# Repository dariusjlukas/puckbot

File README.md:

# puckbot
Puck-shaped robot design files and source code

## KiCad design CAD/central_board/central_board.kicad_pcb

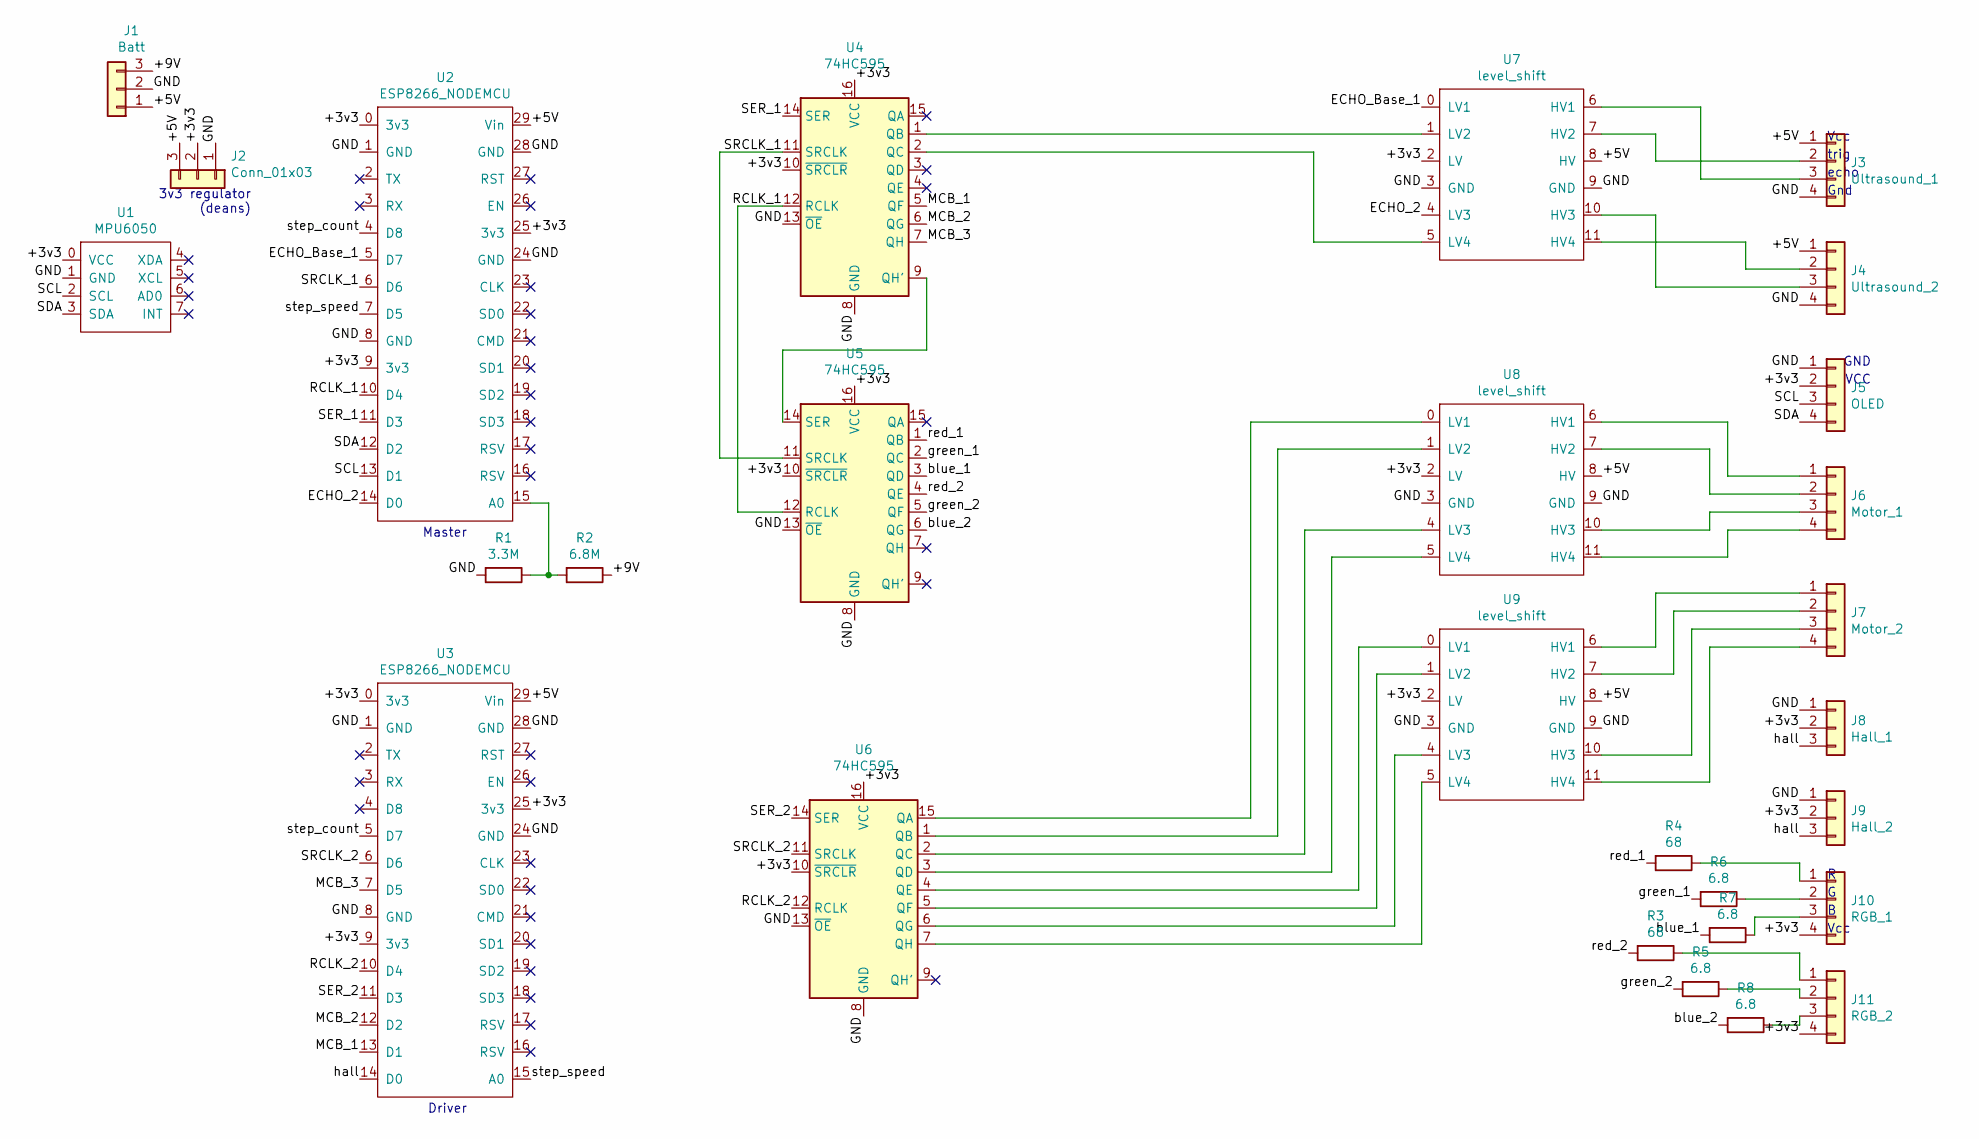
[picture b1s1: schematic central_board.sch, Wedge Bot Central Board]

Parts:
J1: Batt; JST_XHP_3
J2: Conn_01x03; JST_XHP_3
J3: Ultrasound_1; JST_XHP_4
J4: Ultrasound_2; JST_XHP_4
J5: OLED; JST_XHP_4
J6: Motor_1; JST_XHP_4
J7: Motor_2; JST_XHP_4
J8: Hall_1; JST_XHP_3
J9: Hall_2; JST_XHP_3
J10: RGB_1; JST_XHP_4
J11: RGB_2; JST_XHP_4
R1: 3.3M; R_Axial_DIN0207_L6.3mm_D2.5mm_P7.62mm_Horizontal
R2: 6.8M; R_Axial_DIN0207_L6.3mm_D2.5mm_P7.62mm_Horizontal
R3, R4: 68; R_Axial_DIN0207_L6.3mm_D2.5mm_P7.62mm_Horizontal
R5, R6, R7, R8: 6.8; R_Axial_DIN0207_L6.3mm_D2.5mm_P7.62mm_Horizontal
U1: MPU6050
U2, U3: ESP8266_NODEMCU
U4, U5, U6: 74HC595; 74HC595N
U7, U8, U9: level_shift; Level_shift

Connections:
/+3v3: J2.2, J5.2, J8.2, J9.2, J10.4, J11.4, U1.0 (VCC), U2.0 (3v3), U2.9 (3v3), U2.25 (3v3), U3.0 (3v3), U3.9 (3v3), U3.25 (3v3), U4.10 (~SRCLR), U4.16 (VCC), U5.10 (~SRCLR), U5.16 (VCC), U6.10 (~SRCLR), U6.16 (VCC), U7.2 (LV), U8.2 (LV), U9.2 (LV)
/+5V: J1.1, J2.3, J3.1, J4.1, U2.29 (Vin), U3.29 (Vin), U7.8 (HV), U8.8 (HV), U9.8 (HV)
/+9V: J1.3, R2.1
/ECHO_2: U2.14 (D0), U7.4 (LV3)
/ECHO_Base_1: U2.5 (D7), U7.0 (LV1)
/GND: J1.2, J2.1, J3.4, J4.4, J5.1, J8.1, J9.1, R1.2, U1.1 (GND), U2.1 (GND), U2.8 (GND), U2.24 (GND), U2.28 (GND), U3.1 (GND), U3.8 (GND), U3.24 (GND), U3.28 (GND), U4.8 (GND), U4.13 (~OE), U5.8 (GND), U5.13 (~OE), U6.8 (GND), U6.13 (~OE), U7.3 (GND), U7.9 (GND), U8.3 (GND), U8.9 (GND), U9.3 (GND), U9.9 (GND)
/MCB_1: U3.13 (D1), U4.5 (QF)
/MCB_2: U3.12 (D2), U4.6 (QG)
/MCB_3: U3.7 (D5), U4.7 (QH)
/RCLK_1: U2.10 (D4), U4.12 (RCLK), U5.12 (RCLK)
/RCLK_2: U3.10 (D4), U6.12 (RCLK)
/SCL: J5.3, U1.2 (SCL), U2.13 (D1)
/SDA: J5.4, U1.3 (SDA), U2.12 (D2)
/SER_1: U2.11 (D3), U4.14 (SER)
/SER_2: U3.11 (D3), U6.14 (SER)
/SRCLK_1: U2.6 (D6), U4.11 (SRCLK), U5.11 (SRCLK)
/SRCLK_2: U3.6 (D6), U6.11 (SRCLK)
/blue_1: R7.2, U5.3 (QD)
/blue_2: R8.2, U5.6 (QG)
/green_1: R6.2, U5.2 (QC)
/green_2: R5.2, U5.5 (QF)
/hall: J8.3, J9.3, U3.14 (D0)
/red_1: R4.2, U5.1 (QB)
/red_2: R3.2, U5.4 (QE)
/step_count: U2.4 (D8), U3.5 (D7)
/step_speed: U2.7 (D5), U3.15 (A0)
unnamed: J3.2, U7.7 (HV2)
unnamed: J3.3, U7.6 (HV1)
unnamed: J4.2, U7.11 (HV4)
unnamed: J4.3, U7.10 (HV3)
unnamed: J6.1, U8.6 (HV1)
unnamed: J6.2, U8.7 (HV2)
unnamed: J6.3, U8.10 (HV3)
unnamed: J6.4, U8.11 (HV4)
unnamed: J7.1, U9.6 (HV1)
unnamed: J7.2, U9.7 (HV2)
unnamed: J7.3, U9.10 (HV3)
unnamed: J7.4, U9.11 (HV4)
unnamed: J10.1, R4.1
unnamed: J10.2, R6.1
unnamed: J10.3, R7.1
unnamed: J11.1, R3.1
unnamed: J11.2, R5.1
unnamed: J11.3, R8.1
unnamed: R1.1, R2.2, U2.15 (A0)
unnamed: U4.1 (QB), U7.1 (LV2)
unnamed: U4.2 (QC), U7.5 (LV4)
unnamed: U4.9 (QH'), U5.14 (SER)
unnamed: U6.1 (QB), U8.1 (LV2)
unnamed: U6.2 (QC), U8.4 (LV3)
unnamed: U6.3 (QD), U8.5 (LV4)
unnamed: U6.4 (QE), U9.0 (LV1)
unnamed: U6.5 (QF), U9.1 (LV2)
unnamed: U6.6 (QG), U9.4 (LV3)
unnamed: U6.7 (QH), U9.5 (LV4)
unnamed: U6.15 (QA), U8.0 (LV1)

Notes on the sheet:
Master
Driver
Vcc
trig
echo
Gnd
3v3 regulator (deans)
GND
VCC

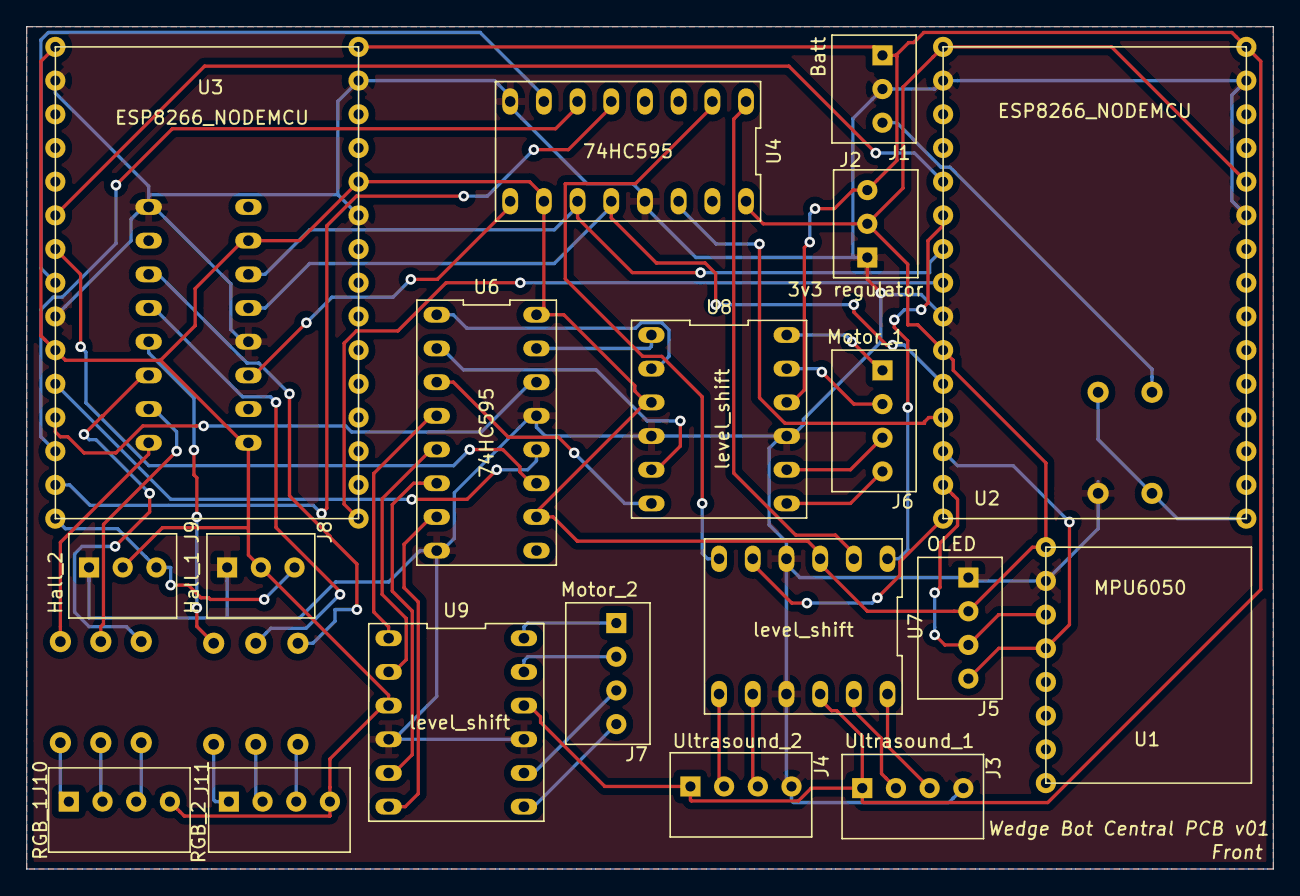
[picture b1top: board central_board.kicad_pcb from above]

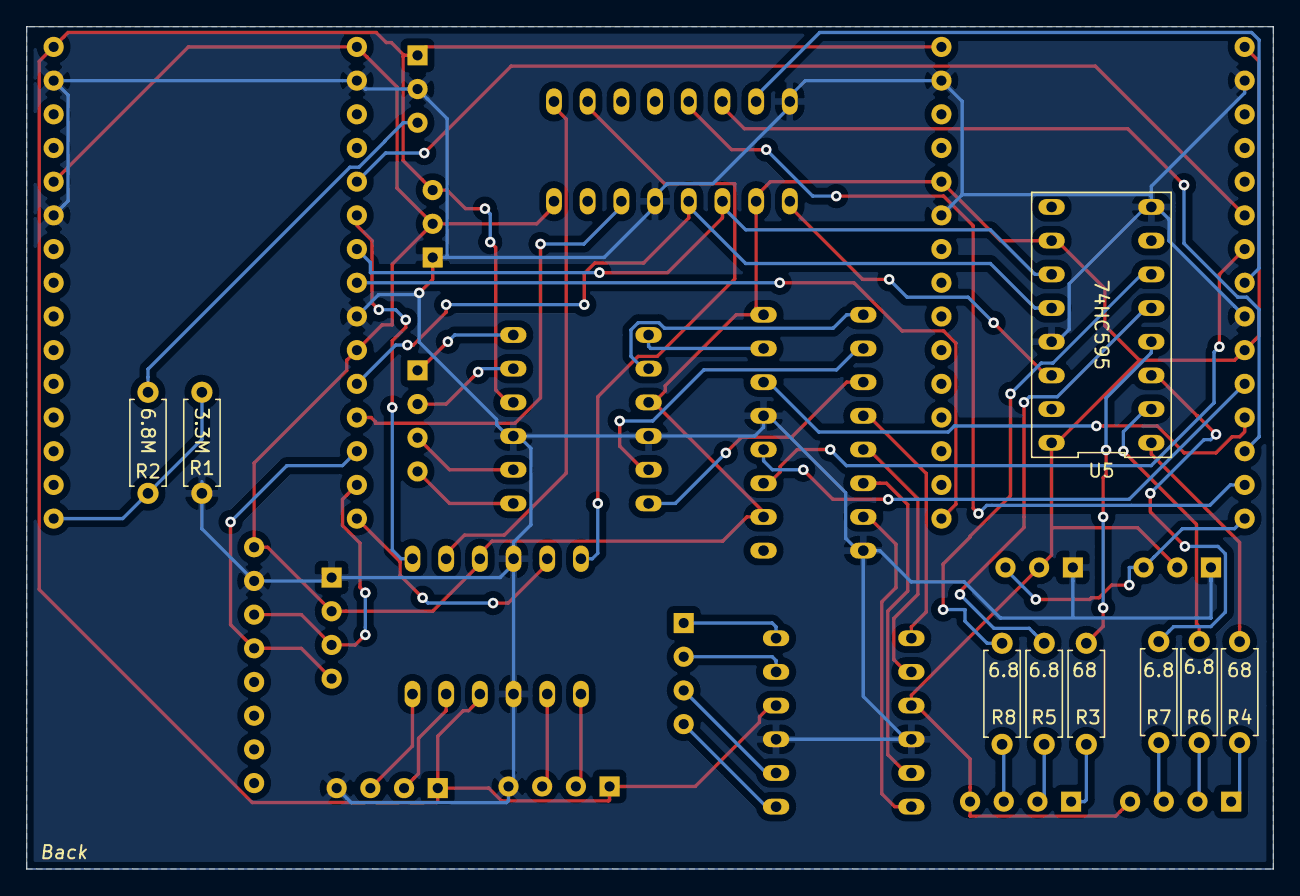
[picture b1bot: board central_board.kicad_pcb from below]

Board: 2 copper layers, 94.0 x 63.5 mm, 28 parts (9 on the bottom side), 56 nets.

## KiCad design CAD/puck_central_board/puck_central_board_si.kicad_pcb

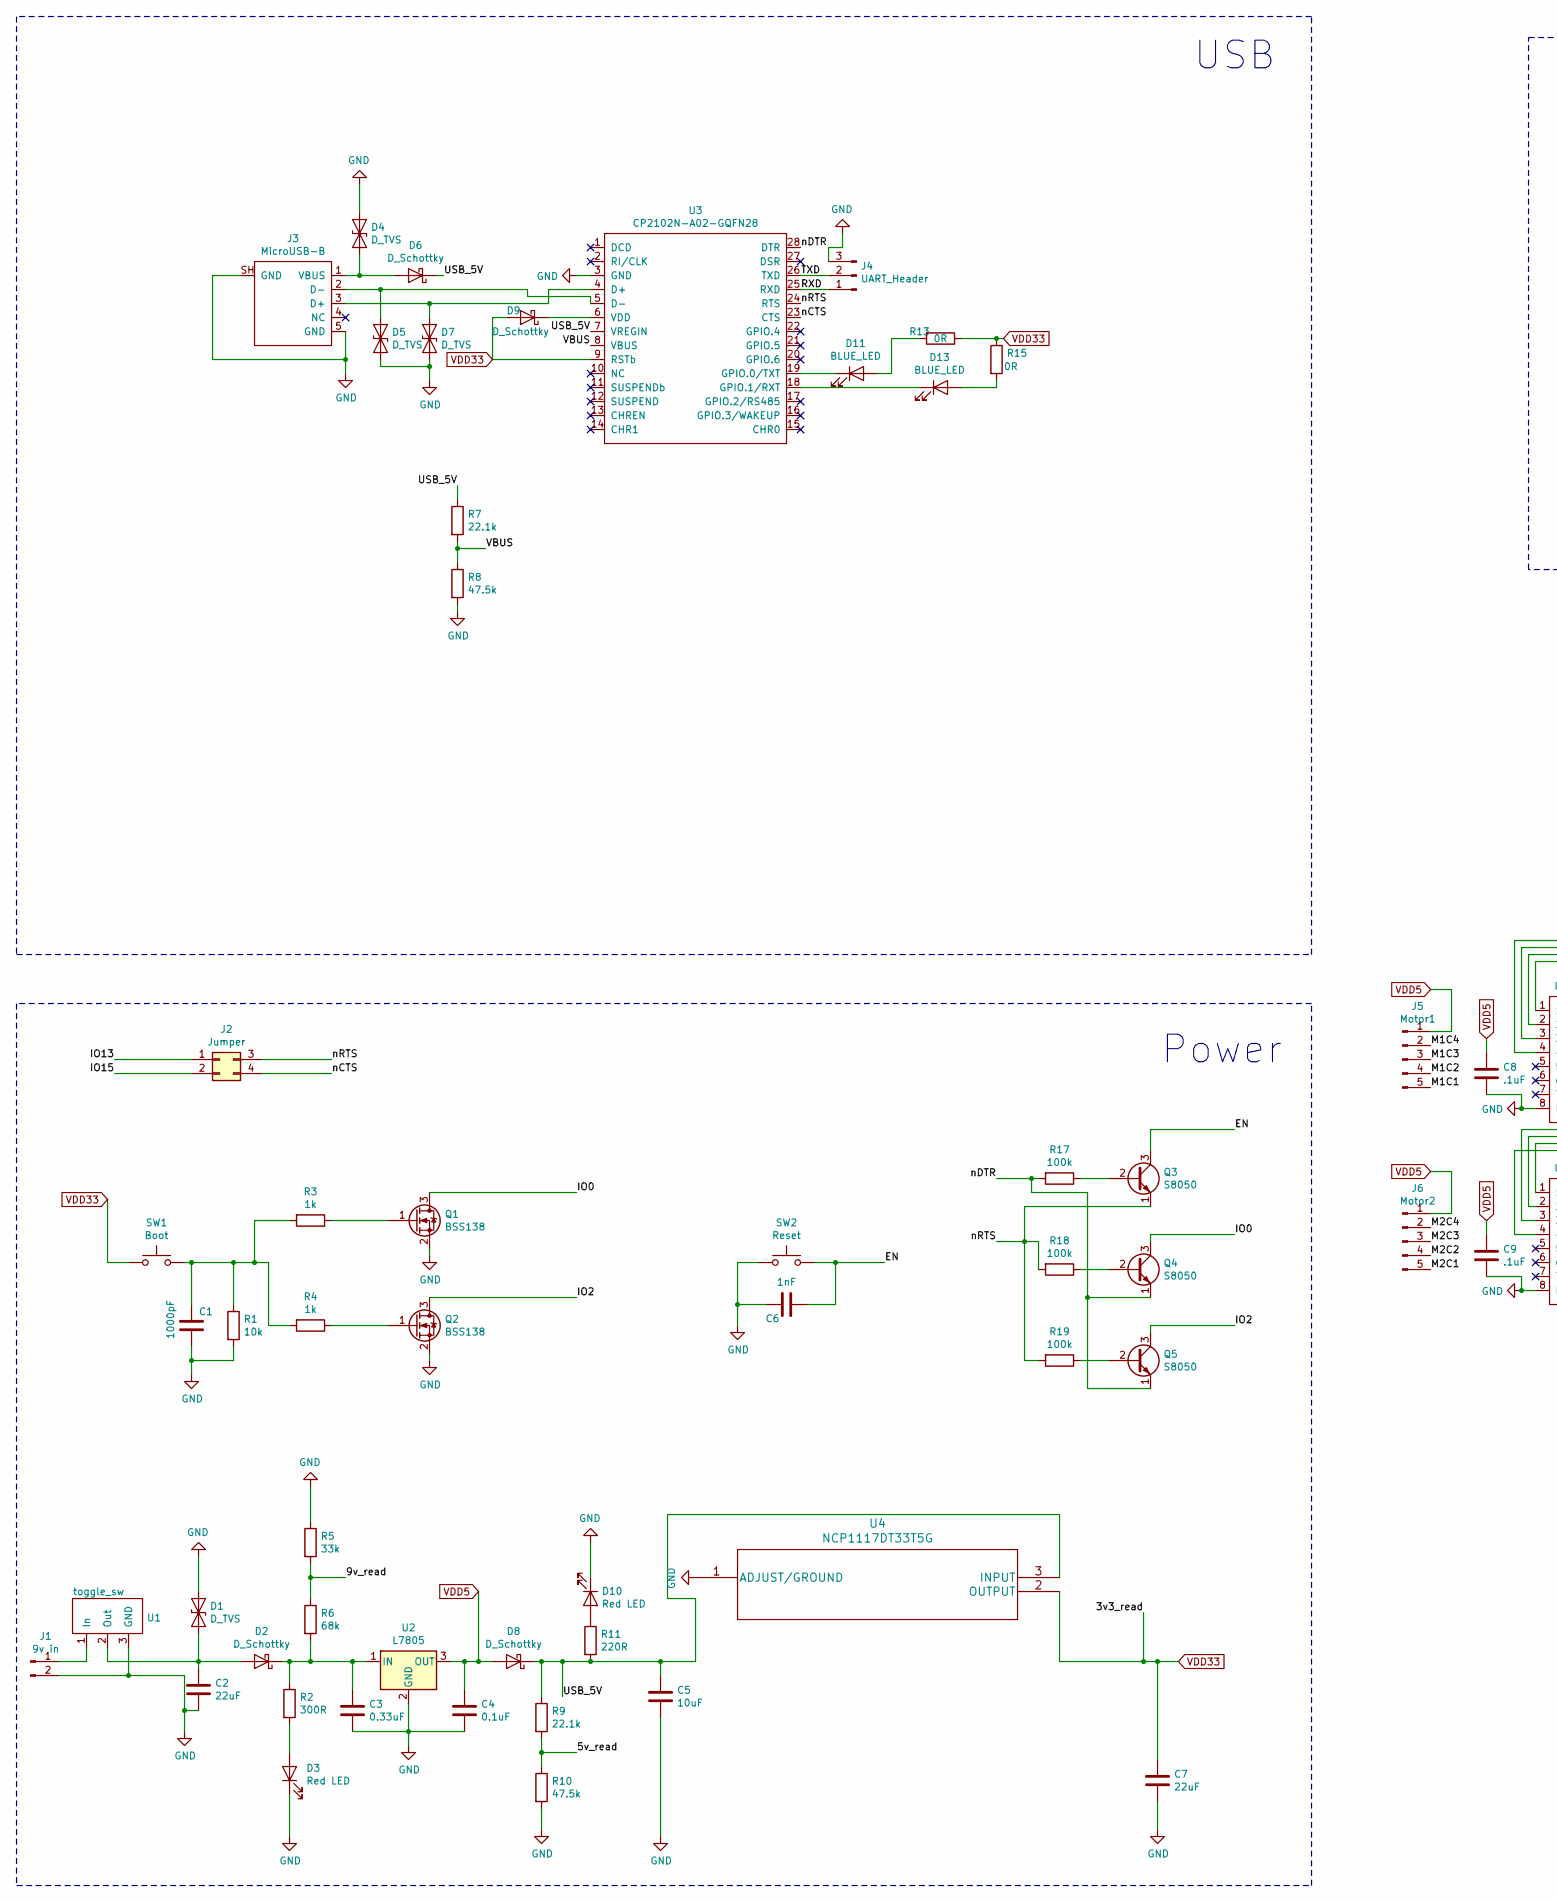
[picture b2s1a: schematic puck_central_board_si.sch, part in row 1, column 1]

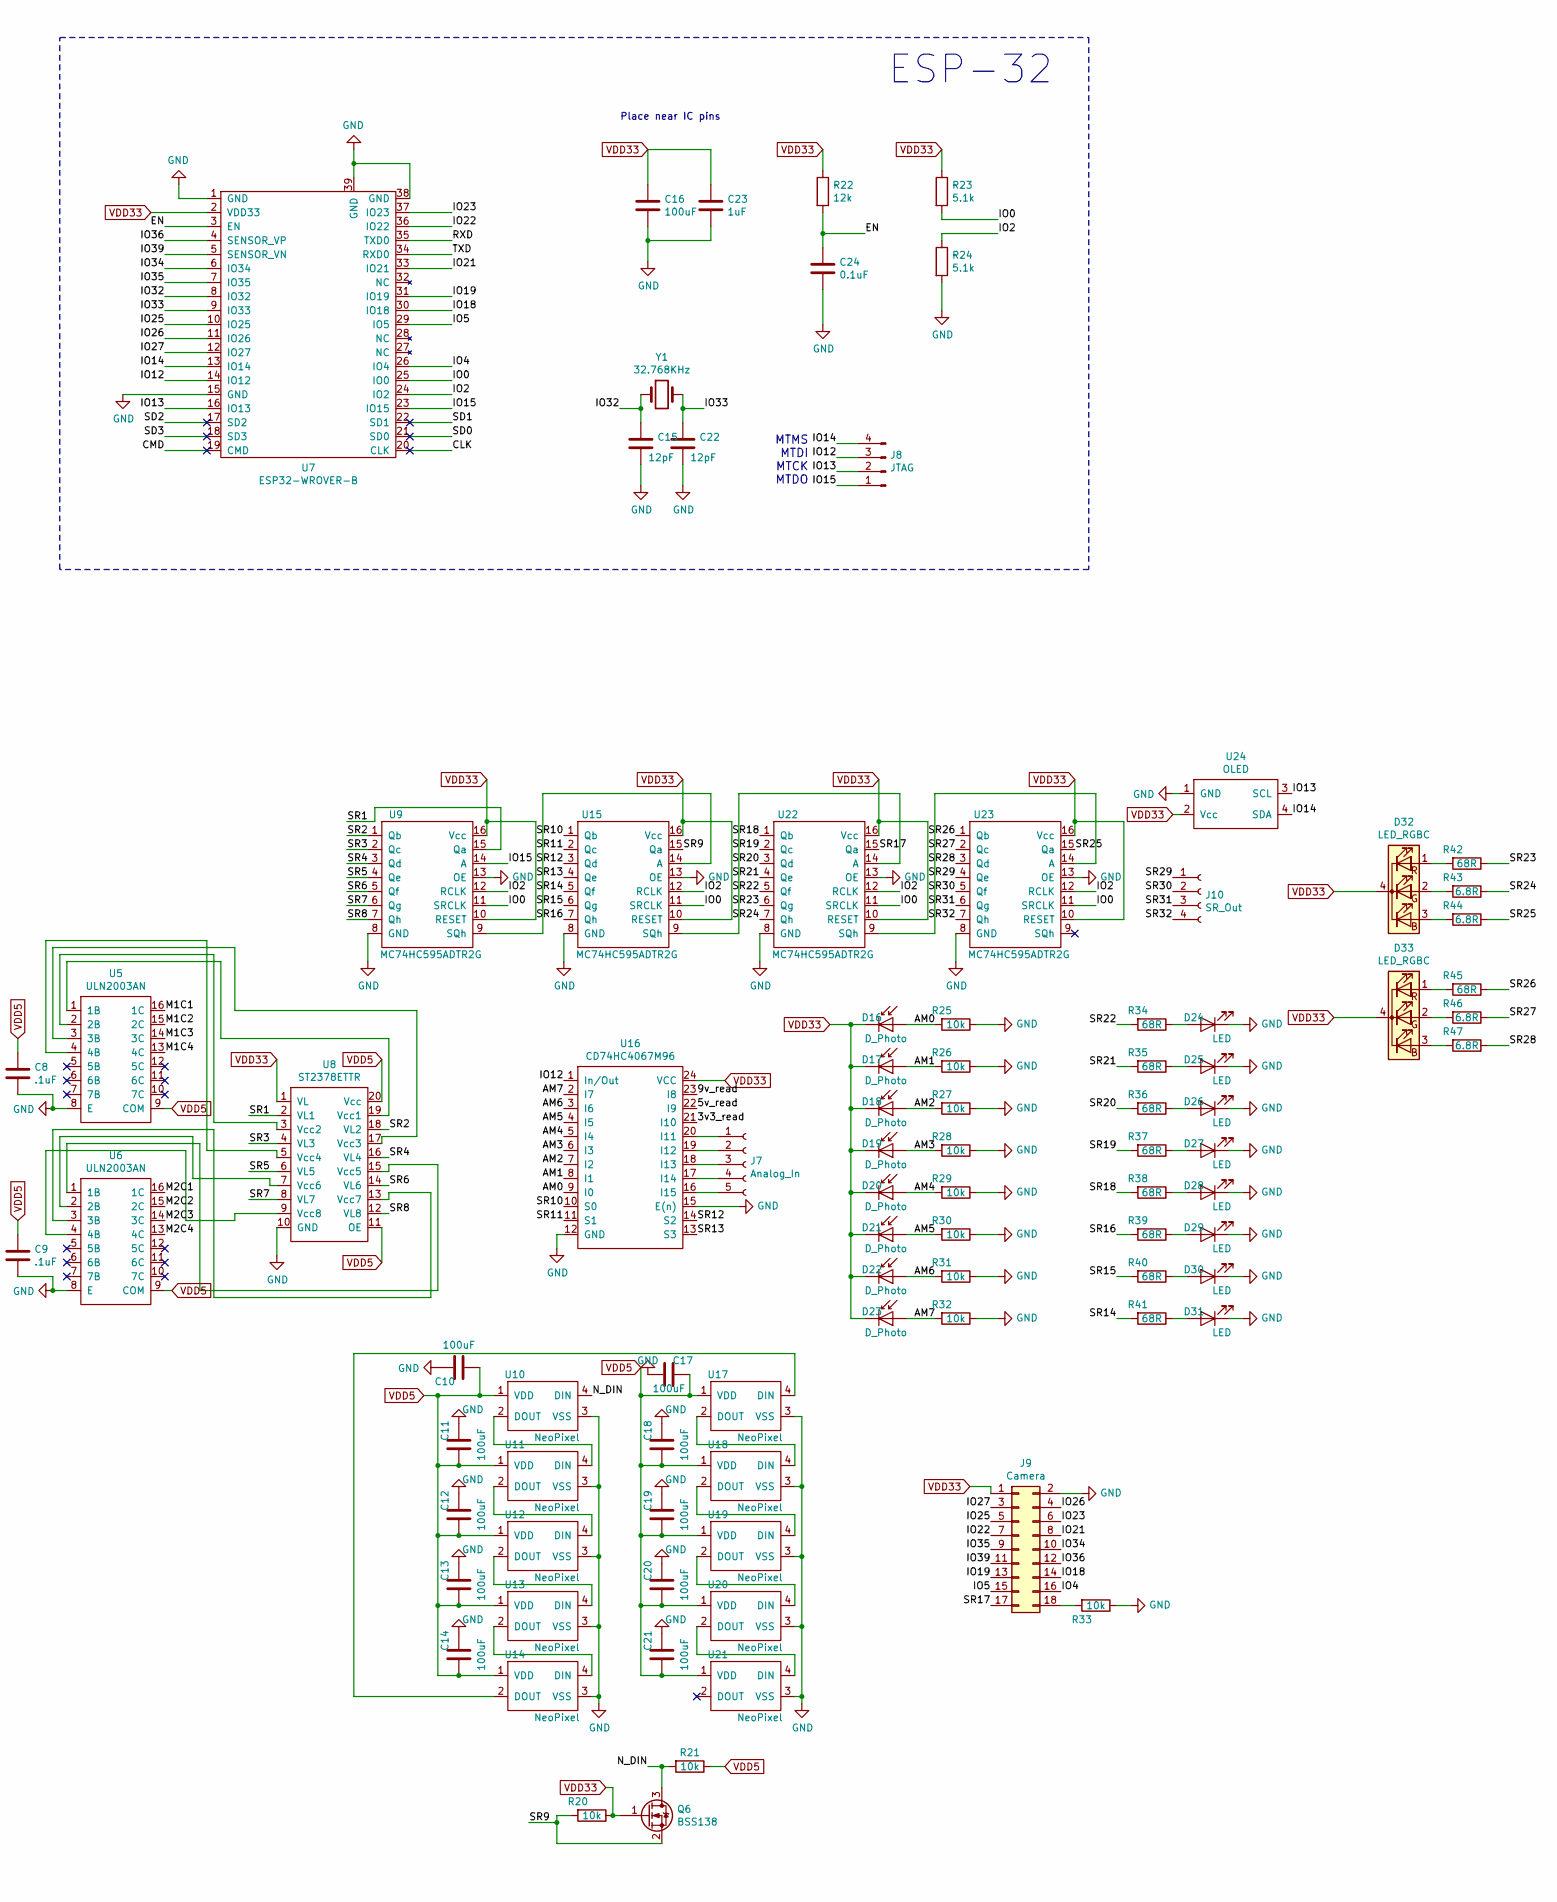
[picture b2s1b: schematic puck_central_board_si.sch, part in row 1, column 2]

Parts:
C1: 1000pF; C_0402_1005Metric
C2, C7: 22uF; C_0805_2012Metric
C3: 0.33uF; C_0201_0603Metric
C4, C24: 0.1uF; C_0402_1005Metric
C5: 10uF; C_1206_3216Metric
C6: 1nF; C_0402_1005Metric
C8, C9: .1uF; C_0402_1005Metric
C10, C11, C12, C13, C14, C16, C17, C18, C19, C20, C21: 100uF; C_1206_3216Metric
C15, C22: 12pF; C_0402_1005Metric
C23: 1uF; C_0603_1608Metric
D1, D4, D5, D7: D_TVS; D_SMA
D2, D6, D8, D9: D_Schottky; D_SMA
D3, D10: Red LED; LED_0603
D11, D13: BLUE_LED; LED_0603
D16, D17, D18, D19, D20, D21, D22, D23: D_Photo; LED_5mm_Radial
D24, D25, D26, D27, D28, D29, D30, D31: LED; LED_5mm_Radial
D32, D33: LED_RGBC; RGB_LED
J1: 9v in; JST_XHP_2
J2: Jumper; Jumper_Header
J3: MicroUSB-B; USB_Micro_B_Female_10118193-0001LF
J4: UART_Header; Deans_2.54_3
J5: Motor1; JST_XHP_5
J6: Motor2; JST_XHP_5
J7: Analog_In; Deans_2.54_5
J8: JTAG; Deans_2.54_4
J9: Camera; camera_connector
J10: SR_Out; Deans_2.54_4
Q1, Q2, Q6: BSS138; SOT-23
Q3, Q4, Q5: S8050; SOT-23
R1, R20, R21, R25, R26, R27, R28, R29, R30, R31, R32, R33: 10k; R_0402_1005Metric
R2: 300R; R_0402_1005Metric
R3, R4: 1k; R_0402_1005Metric
R5: 33k; R_0402_1005Metric
R6: 68k; R_0603_1608Metric_Pad1.05x0.95mm_HandSolder
R7, R9: 22.1k; R_0402_1005Metric
R8, R10: 47.5k; R_0402_1005Metric
R11: 220R; R_0402_1005Metric
R13, R15: 0R; R_0402_1005Metric
R17, R18, R19: 100k; R_0402_1005Metric
R22: 12k; R_0402_1005Metric
R23, R24: 5.1k; R_0402_1005Metric
R34, R35, R36, R37, R38, R39, R40, R41, R42, R45: 68R; R_0603_1608Metric_Pad1.05x0.95mm_HandSolder
R43, R44, R46, R47: 6.8R; R_0603_1608Metric
SW1: Boot; SW_Push_1P1T_NO_6x6mm_H9.5mm
SW2: Reset; SW_Push_1P1T_NO_6x6mm_H9.5mm
U1: toggle_sw; Deans_2.54_3
U2: L7805; TO-218-3_Horizontal_TabDown
U3: CP2102N-A02-GQFN28; CP2102_QFN28
U4: NCP1117DT33T5G
U5, U6: ULN2003AN; Socket_DIP-16_7.62mm_Conn
U7: ESP32-WROVER-B
U8: ST2378ETTR; ST2378
U9, U15, U22, U23: MC74HC595ADTR2G
U10, U11, U12, U13, U14, U17, U18, U19, U20, U21: NeoPixel
U16: CD74HC4067M96
U24: OLED; Deans_2.54_4
Y1: 32.768KHz; FC-135R

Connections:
/5v_read: R9.2, R10.1, U16.22 (I9)
/9v_read: R5.2, R6.1, U16.23 (I8)
/AM0: D16.2 (A), R25.2, U16.9 (I0)
/AM1: D17.2 (A), R26.2, U16.8 (I1)
/AM2: D18.2 (A), R27.2, U16.7 (I2)
/AM3: D19.2 (A), R28.2, U16.6 (I3)
/AM4: D20.2 (A), R29.2, U16.5 (I4)
/AM5: D21.2 (A), R30.2, U16.4 (I5)
/AM6: D22.2 (A), R31.2, U16.3 (I6)
/AM7: D23.2 (A), R32.2, U16.2 (I7)
/CLK: U7.20 (CLK)
/CMD: U7.19 (CMD)
/EN: C6.1, C24.1, Q3.3 (C), R22.2, SW2.2, U7.3 (EN)
/IO0: Q1.3 (D), Q4.3 (C), R23.2, U7.25 (IO0), U9.11 (SRCLK), U15.11 (SRCLK), U22.11 (SRCLK), U23.11 (SRCLK)
/IO2: Q2.3 (D), Q5.3 (C), R24.1, U7.24 (IO2), U9.12 (RCLK), U15.12 (RCLK), U22.12 (RCLK), U23.12 (RCLK)
/IO4: J9.16, U7.26 (IO4)
/IO5: J9.15, U7.29 (IO5)
/IO12: J8.3, U7.14 (IO12), U16.1 (In/Out)
/IO13: J2.1, J8.2, U7.16 (IO13), U24.3 (SCL)
/IO14: J8.4, U7.13 (IO14), U24.4 (SDA)
/IO15: J2.2, J8.1, U7.23 (IO15), U9.14 (A)
/IO18: J9.14, U7.30 (IO18)
/IO19: J9.13, U7.31 (IO19)
/IO21: J9.8, U7.33 (IO21)
/IO22: J9.7, U7.36 (IO22)
/IO23: J9.6, U7.37 (IO23)
/IO25: J9.5, U7.10 (IO25)
/IO26: J9.4, U7.11 (IO26)
/IO27: J9.3, U7.12 (IO27)
/IO32: C15.1, U7.8 (IO32), Y1.1
/IO33: C22.1, U7.9 (IO33), Y1.2
/IO34: J9.10, U7.6 (IO34)
/IO35: J9.9, U7.7 (IO35)
/IO36: J9.12, U7.4 (SENSOR_VP)
/IO39: J9.11, U7.5 (SENSOR_VN)
/M1C1: J5.5, U5.16 (1C)
/M1C2: J5.4, U5.15 (2C)
/M1C3: J5.3, U5.14 (3C)
/M1C4: J5.2, U5.13 (4C)
/M2C1: J6.5, U6.16 (1C)
/M2C2: J6.4, U6.15 (2C)
/M2C3: J6.3, U6.14 (3C)
/M2C4: J6.2, U6.13 (4C)
/N_DIN: Q6.3 (D), R21.2, U10.4 (DIN)
/RXD: J4.1, U3.25 (RXD), U7.35 (TXD0)
/SD0: U7.21 (SD0)
/SD1: U7.22 (SD1)
/SD2: U7.17 (SD2)
/SD3: U7.18 (SD3)
/SR1: U8.2 (VL1), U9.15 (Qa)
/SR2: U8.18 (VL2), U9.1 (Qb)
/SR3: U8.4 (VL3), U9.2 (Qc)
/SR4: U8.16 (VL4), U9.3 (Qd)
/SR5: U8.6 (VL5), U9.4 (Qe)
/SR6: U8.14 (VL6), U9.5 (Qf)
/SR7: U8.8 (VL7), U9.6 (Qg)
/SR8: U8.12 (VL8), U9.7 (Qh)
/SR9: Q6.2 (S), R20.2, U15.15 (Qa)
/SR10: U15.1 (Qb), U16.10 (S0)
/SR11: U15.2 (Qc), U16.11 (S1)
/SR12: U15.3 (Qd), U16.14 (S2)
/SR13: U15.4 (Qe), U16.13 (S3)
/SR14: R41.2, U15.5 (Qf)
/SR15: R40.2, U15.6 (Qg)
/SR16: R39.2, U15.7 (Qh)
/SR17: J9.17, U22.15 (Qa)
/SR18: R38.2, U22.1 (Qb)
/SR19: R37.2, U22.2 (Qc)
/SR20: R36.2, U22.3 (Qd)
/SR21: R35.2, U22.4 (Qe)
/SR22: R34.2, U22.5 (Qf)
/SR23: R42.1, U22.6 (Qg)
/SR24: R43.1, U22.7 (Qh)
/SR25: R44.1, U23.15 (Qa)
/SR26: R45.1, U23.1 (Qb)
/SR27: R46.1, U23.2 (Qc)
/SR28: R47.1, U23.3 (Qd)
/SR29: J10.1, U23.4 (Qe)
/SR30: J10.2, U23.5 (Qf)
/SR31: J10.3, U23.6 (Qg)
/SR32: J10.4, U23.7 (Qh)
/TXD: J4.2, U3.26 (TXD), U7.34 (RXD0)
/USB_5V: C5.1, D6.1 (K), D8.1 (K), R7.1, R9.1, R11.2, U3.7 (VREGIN), U4.3 (INPUT)
/VBUS: R7.2, R8.1, U3.8 (VBUS)
/nCTS: J2.4, U3.23 (CTS)
/nDTR: Q4.1 (E), Q5.1 (E), R17.2, U3.28 (DTR)
/nRTS: J2.3, Q3.1 (E), R18.2, R19.2, U3.24 (RTS)
GND: C1.2, C2.2, C3.2, C4.2, C5.2, C6.2, C7.2, C8.2, C9.2, C10.2, C11.2, C12.2, C13.2, C14.2, C15.2, C16.2, C17.1, C18.2, C19.2, C20.2, C21.2, C22.2, C23.2, C24.2, D1.1 (A1), D3.1 (K), D4.1 (A1), D5.2 (A2), D7.2 (A2), D10.1 (K), D24.1 (K), D25.1 (K), D26.1 (K), D27.1 (K), D28.1 (K), D29.1 (K), D30.1 (K), D31.1 (K), J1.2, J3.5 (GND), J3.SH (GND), J4.3, J9.2, Q1.2 (S), Q2.2 (S), R1.2, R5.1, R8.2, R10.2, R24.2, R25.1, R26.1, R27.1, R28.1, R29.1, R30.1, R31.1, R32.1, R33.1, SW2.1, U1.3 (GND), U2.2 (GND), U3.3 (GND), U4.1 (ADJUST/GROUND), U5.8 (E), U6.8 (E), U7.1 (GND), U7.15 (GND), U7.38 (GND), U7.39 (GND), U8.10 (GND), U9.8 (GND), U9.13 (OE), U10.3 (VSS), U11.3 (VSS), U12.3 (VSS), U13.3 (VSS), U14.3 (VSS), U15.8 (GND), U15.13 (OE), U16.12 (GND), U16.15 (E(n)), U17.3 (VSS), U18.3 (VSS), U19.3 (VSS), U20.3 (VSS), U21.3 (VSS), U22.8 (GND), U22.13 (OE), U23.8 (GND), U23.13 (OE), U24.1 (GND)
unnamed: C1.1, R1.1, R3.2, R4.2, SW1.2
unnamed: C2.1, D1.2 (A2), D2.2 (A), U1.2 (Out)
unnamed: C3.1, D2.1 (K), R2.1, R6.2, U2.1 (IN)
unnamed: D3.2 (A), R2.2
unnamed: D4.2 (A2), D6.2 (A), J3.1 (VBUS)
unnamed: D5.1 (A1), J3.2 (D-), U3.5 (D-)
unnamed: D7.1 (A1), J3.3 (D+), U3.4 (D+)
unnamed: D9.1 (K), U3.6 (VDD)
unnamed: D10.2 (A), R11.1
unnamed: D11.1 (K), U3.19 (GPIO.0/TXT)
unnamed: D11.2 (A), R13.2
unnamed: D13.1 (K), U3.18 (GPIO.1/RXT)
unnamed: D13.2 (A), R15.2
unnamed: D24.2 (A), R34.1
unnamed: D25.2 (A), R35.1
unnamed: D26.2 (A), R36.1
unnamed: D27.2 (A), R37.1
unnamed: D28.2 (A), R38.1
unnamed: D29.2 (A), R39.1
unnamed: D30.2 (A), R40.1
unnamed: D31.2 (A), R41.1
unnamed: D32.1 (RA), R42.2
unnamed: D32.2 (GA), R43.2
unnamed: D32.3 (BA), R44.2
unnamed: D33.1 (RA), R45.2
unnamed: D33.2 (GA), R46.2
unnamed: D33.3 (BA), R47.2
unnamed: J1.1, U1.1 (In)
unnamed: J7.1, U16.20 (I11)
unnamed: J7.2, U16.19 (I12)
unnamed: J7.3, U16.18 (I13)
unnamed: J7.4, U16.17 (I14)
unnamed: J7.5, U16.16 (I15)
unnamed: J9.18, R33.2
unnamed: Q1.1 (G), R3.1
unnamed: Q2.1 (G), R4.1
unnamed: Q3.2 (B), R17.1
unnamed: Q4.2 (B), R18.1
unnamed: Q5.2 (B), R19.1
unnamed: U5.1 (1B), U8.19 (Vcc1)
unnamed: U5.2 (2B), U8.3 (Vcc2)
unnamed: U5.3 (3B), U8.17 (Vcc3)
unnamed: U5.4 (4B), U8.5 (Vcc4)
unnamed: U6.1 (1B), U8.15 (Vcc5)
unnamed: U6.2 (2B), U8.7 (Vcc6)
unnamed: U6.3 (3B), U8.13 (Vcc7)
unnamed: U6.4 (4B), U8.9 (Vcc8)
unnamed: U10.2 (DOUT), U11.4 (DIN)
unnamed: U11.2 (DOUT), U12.4 (DIN)
unnamed: U12.2 (DOUT), U13.4 (DIN)
unnamed: U13.2 (DOUT), U14.4 (DIN)
unnamed: U14.2 (DOUT), U17.4 (DIN)
unnamed: U15.9 (SQh), U22.14 (A)
unnamed: U9.9 (SQh), U15.14 (A)
unnamed: U17.2 (DOUT), U18.4 (DIN)
unnamed: U18.2 (DOUT), U19.4 (DIN)
unnamed: U19.2 (DOUT), U20.4 (DIN)
unnamed: U20.2 (DOUT), U21.4 (DIN)
unnamed: U22.9 (SQh), U23.14 (A)
VDD5: C4.1, C8.1, C9.1, C10.1, C11.1, C12.1, C13.1, C14.1, C17.2, C18.1, C19.1, C20.1, C21.1, D8.2 (A), J5.1, J6.1, R21.1, U2.3 (OUT), U5.9 (COM), U6.9 (COM), U8.11 (OE), U8.20 (Vcc), U10.1 (VDD), U11.1 (VDD), U12.1 (VDD), U13.1 (VDD), U14.1 (VDD), U17.1 (VDD), U18.1 (VDD), U19.1 (VDD), U20.1 (VDD), U21.1 (VDD)
VDD33: C7.1, C16.1, C23.1, D9.2 (A), D16.1 (K), D17.1 (K), D18.1 (K), D19.1 (K), D20.1 (K), D21.1 (K), D22.1 (K), D23.1 (K), D32.4 (K), D33.4 (K), J9.1, Q6.1 (G), R13.1, R15.1, R20.1, R22.1, R23.1, SW1.1, U3.9 (RSTb), U4.2 (OUTPUT), U7.2 (VDD33), U8.1 (VL), U9.10 (RESET), U9.16 (Vcc), U15.10 (RESET), U15.16 (Vcc), U16.21 (I10), U16.24 (VCC), U22.10 (RESET), U22.16 (Vcc), U23.10 (RESET), U23.16 (Vcc), U24.2 (Vcc)

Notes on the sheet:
Place near IC pins
Power
ESP-32
USB
MTMS MTDI MTCK MTDO

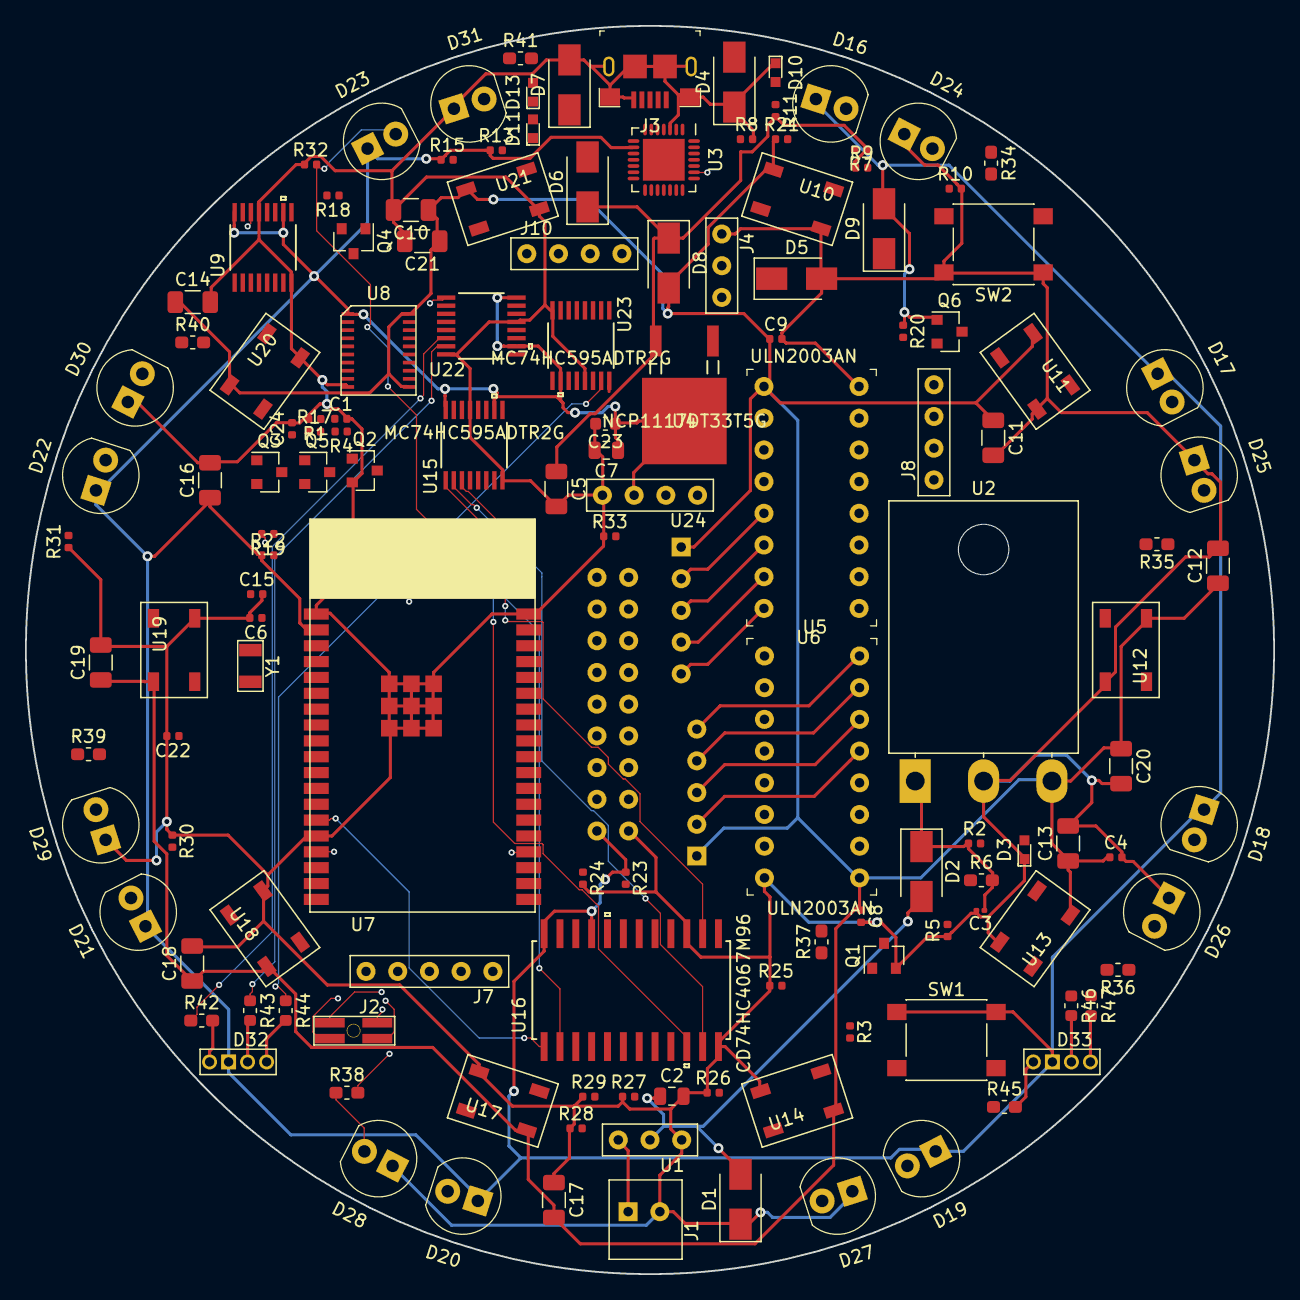
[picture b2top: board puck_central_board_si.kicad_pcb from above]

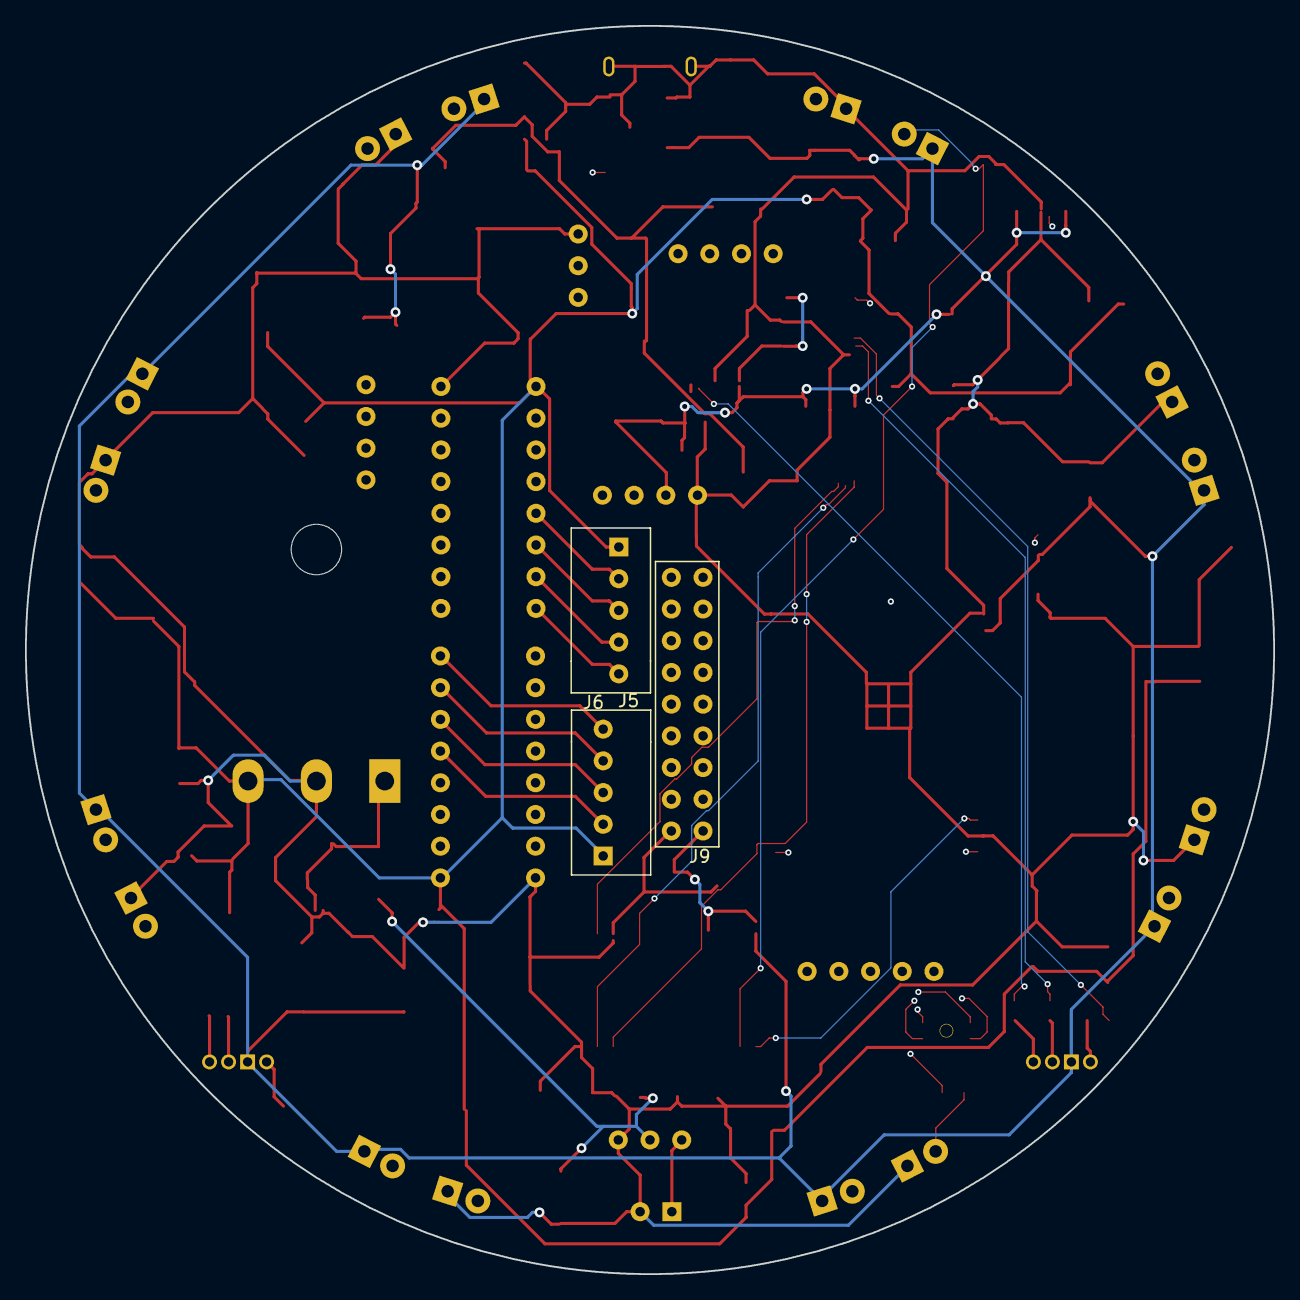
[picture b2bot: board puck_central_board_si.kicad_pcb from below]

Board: 4 copper layers, 100.0 x 100.0 mm, 141 parts (3 on the bottom side), 143 nets.

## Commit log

2020-02-07 Added the initial CAD files
2020-02-07 Added online documentation for the esp32 processor

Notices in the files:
CAD/central_board/central_board.kicad_pcb:
License: CC BY 4.0
CAD/central_board/central_board.sch:
creativecommons.org/licenses/by/4.0
parts and their libraries:
Copyright 2016 Accelerated Designs. All rights reserved.
